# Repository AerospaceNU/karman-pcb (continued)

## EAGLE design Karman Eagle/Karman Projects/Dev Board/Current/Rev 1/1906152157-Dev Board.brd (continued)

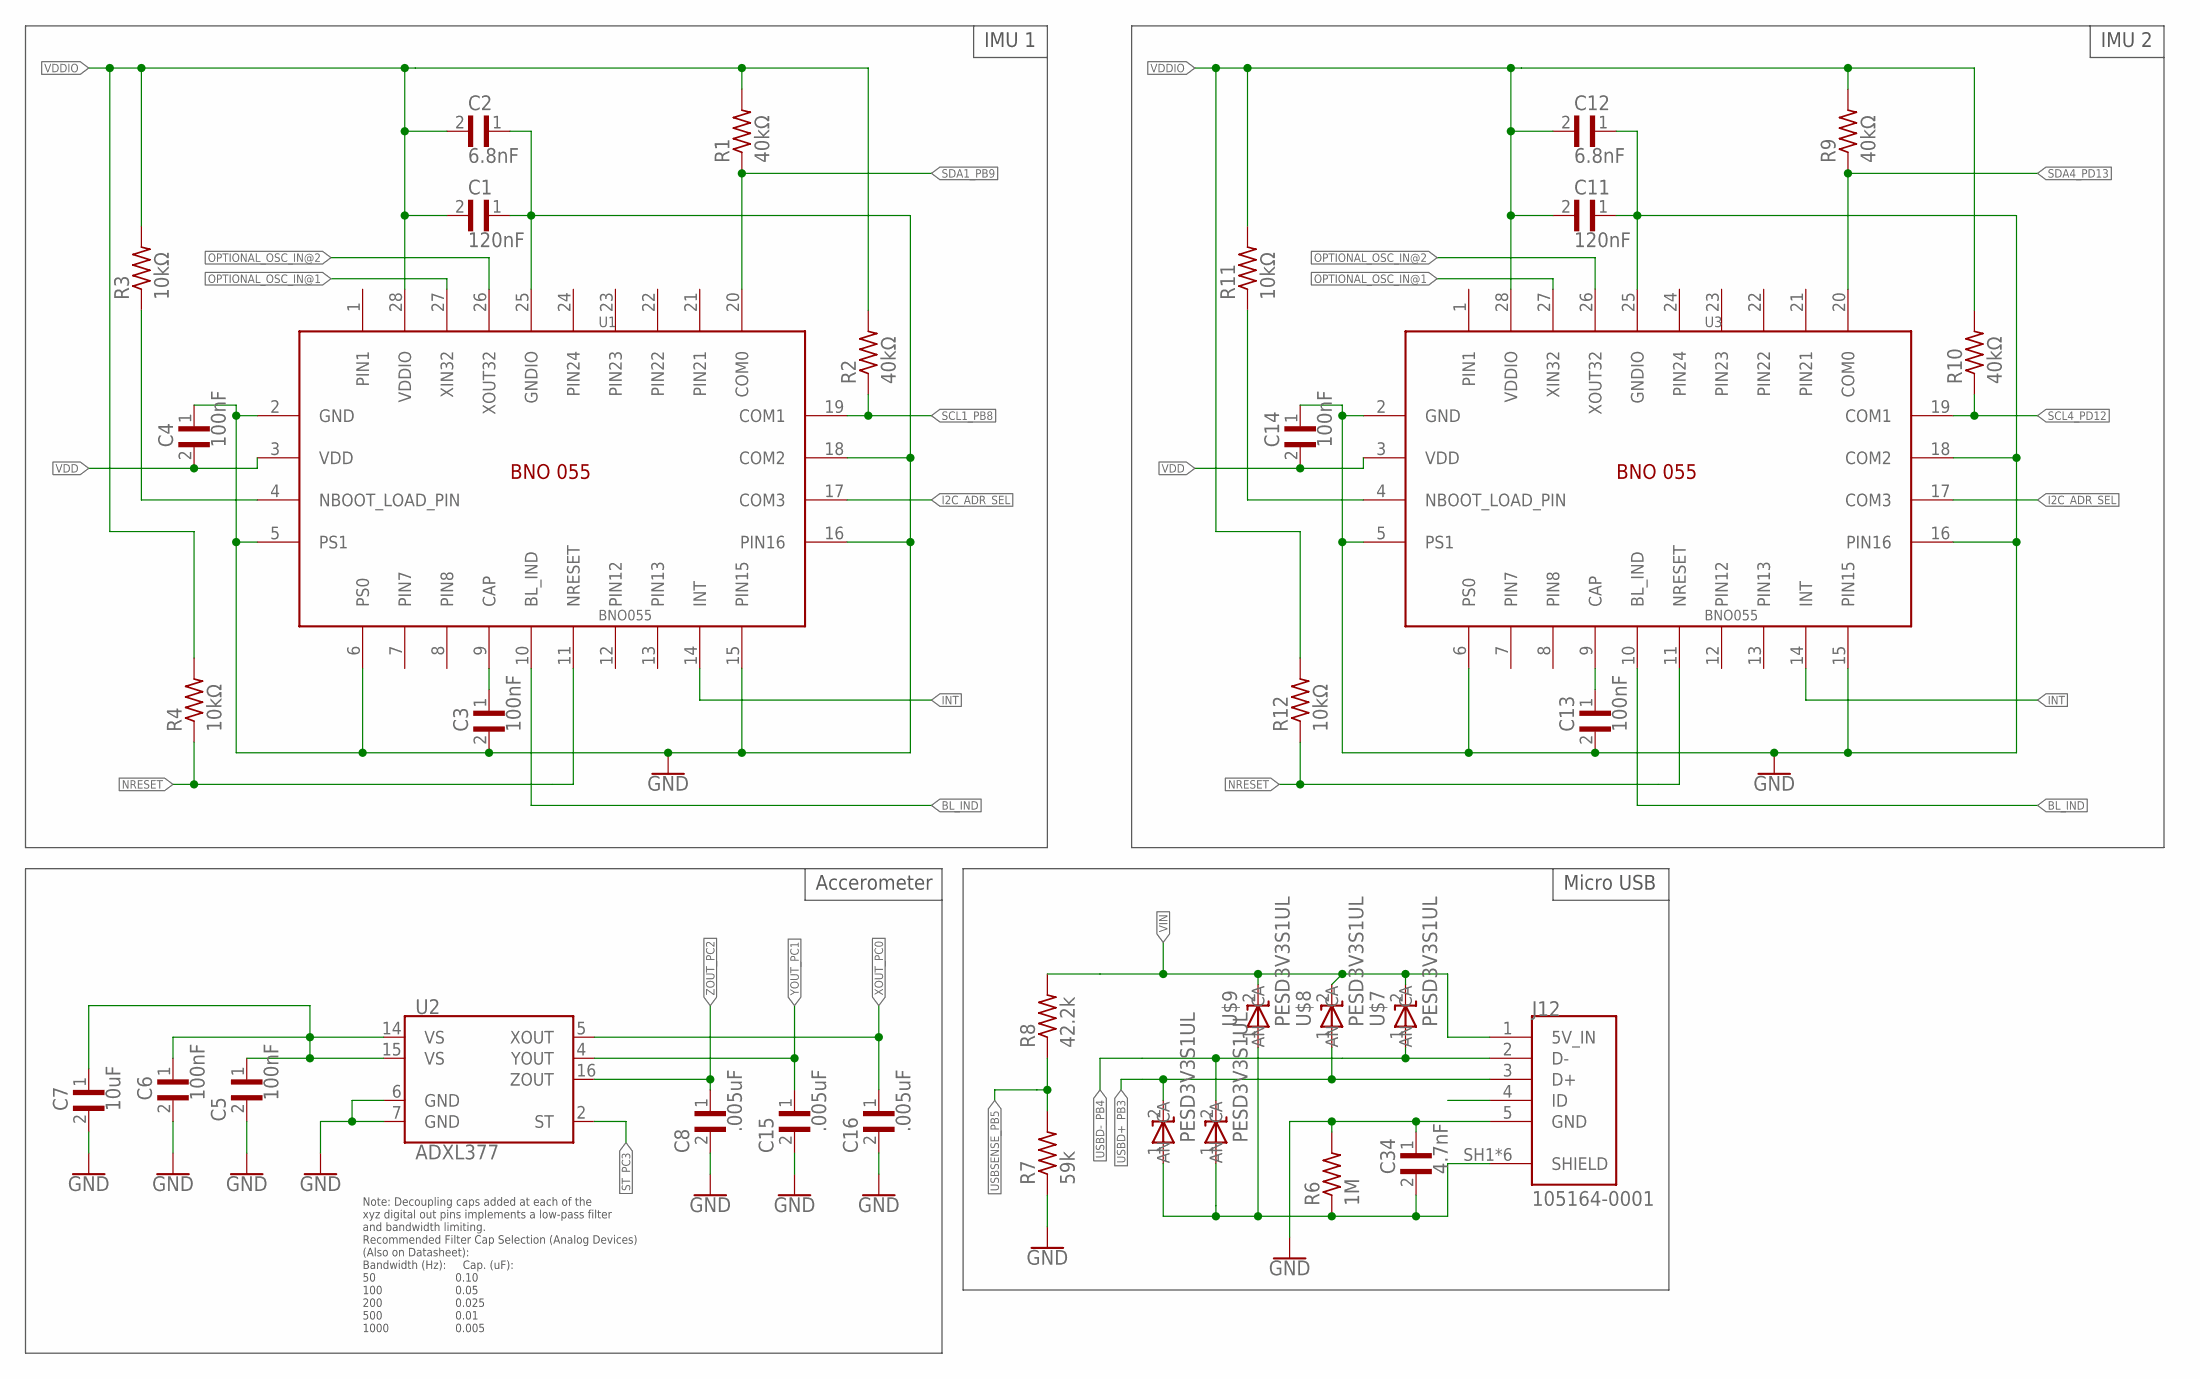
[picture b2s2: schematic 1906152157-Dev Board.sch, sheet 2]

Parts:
C1, C11: 120nF; CAPC1608X95N
C2, C12: 6.8nF; CAPC1608X95N
C3, C4, C5, C6, C13, C14: 100nF; CAPC1608X95N
C7: 10uF; CAPC1608X95N
C8, C15, C16: .005uF; CAPC1608X95N
C34: 4.7nF; CAPC1608X95N
J12: 105164-0001; MOLEX_105164-0001
R1, R2, R9, R10: 40kΩ; RESC1608X50N
R3, R4, R11, R12: 10kΩ; RESC1608X50N
R6: 1M; RESC1608X50N
R7: 59k; RESC1608X50N
R8: 42.2k; RESC1608X50N
U1, U3: BNO055; LGA28R50P4X10_380X520X100
U2: ADXL377; LFCSP-16-3X3
U$7, U$8, U$9, U$10, U$11: PESD3V3S1UL; SOD882

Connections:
BL_IND: U1.10 (BL_IND), U3.10 (BL_IND)
GND: C1.1, C2.1, C3.2, C4.1, C5.2, C6.2, C7.2, C8.2, C11.1, C12.1, C13.2, C14.1, C15.2, C16.2, C34.1, J12.5 (GND), R6.2, R7.1, U1.2 (GND), U1.5 (PS1), U1.6 (PS0), U1.15 (PIN15), U1.16 (PIN16), U1.18 (COM2), U1.25 (GNDIO), U2.6 (GND), U2.7 (GND), U3.2 (GND), U3.5 (PS1), U3.6 (PS0), U3.15 (PIN15), U3.16 (PIN16), U3.18 (COM2), U3.25 (GNDIO); also elsewhere on the board
I2C_ADR_SEL: U1.17 (COM3), U3.17 (COM3)
INT: U1.14 (INT), U3.14 (INT)
unnamed: C3.1, U1.9 (CAP)
unnamed: R3.1, U1.4 (NBOOT_LOAD_PIN)
unnamed: C13.1, U3.9 (CAP)
unnamed: R11.1, U3.4 (NBOOT_LOAD_PIN)
unnamed: C5.1, C6.1, C7.1, U2.14 (VS), U2.15 (VS)
unnamed: C34.2, J12.SH1 (SHIELD), J12.SH2 (SHIELD), J12.SH3 (SHIELD), J12.SH4 (SHIELD), J12.SH5 (SHIELD), J12.SH6 (SHIELD), R6.1, U$9.1 (CA), U$10.1 (CA), U$11.1 (CA)
NRESET: R4.1, R12.1, U1.11 (NRESET), U3.11 (NRESET)
OPTIONAL_OSC_IN@1: U1.27 (XIN32), U3.27 (XIN32)
OPTIONAL_OSC_IN@2: U1.26 (XOUT32), U3.26 (XOUT32)
PIN7: U1.7 (PIN7), U3.7 (PIN7)
PIN8: U1.8 (PIN8), U3.8 (PIN8)
PIN21: U1.21 (PIN21), U3.21 (PIN21)
PIN22: U1.22 (PIN22), U3.22 (PIN22)
PIN23: U1.23 (PIN23), U3.23 (PIN23)
PIN24: U1.24 (PIN24), U3.24 (PIN24)
SCL1_PB8: R2.1, U1.19 (COM1); also elsewhere on the board
SCL4_PD12: R10.1, U3.19 (COM1); also elsewhere on the board
SDA1_PB9: R1.1, U1.20 (COM0); also elsewhere on the board
SDA4_PD13: R9.1, U3.20 (COM0); also elsewhere on the board
ST_PC3: U2.2 (ST); also elsewhere on the board
USBD+_PB3: J12.3 (D+), U$8.1 (CA), U$11.2 (AN); also elsewhere on the board
USBD-_PB4: J12.2 (D-), U$7.1 (CA), U$10.2 (AN); also elsewhere on the board
USBSENSE_PB5: R7.2, R8.1; also elsewhere on the board
VDD: C4.2, C14.2, U1.3 (VDD), U3.3 (VDD)
VDDIO: C1.2, C2.2, C11.2, C12.2, R1.2, R2.2, R3.2, R4.2, R9.2, R10.2, R11.2, R12.2, U1.28 (VDDIO), U3.28 (VDDIO)
VIN: J12.1 (5V_IN), R8.2, U$7.2 (AN), U$8.2 (AN), U$9.2 (AN); also elsewhere on the board
XOUT_PC0: C16.1, U2.5 (XOUT); also elsewhere on the board
YOUT_PC1: C15.1, U2.4 (YOUT); also elsewhere on the board
ZOUT_PC2: C8.1, U2.16 (ZOUT); also elsewhere on the board

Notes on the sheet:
IMU 1
IMU 2
Note: Decoupling caps added at each of the xyz digital out pins implements a low-pass filter and bandwidth limiting. Recommended Filter Cap Selection (Analog Devices) (Also on Datasheet): Bandwidth (Hz): Cap. (uF): 50 0.10 100 0.05 200 0.025 500 0.01 1000 0.005
Accerometer
Micro USB

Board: 2 copper layers, 73 parts (1 on the bottom side), 78 nets, no tracks yet.

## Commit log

2019-05-06 David Antaki initial commit
2019-05-08 5/7/19-Updated FRIDAY Board
2019-05-14 5/13/19 Dev board update
2019-05-14 5/13/19 10:08PM Dev board update
2019-05-15 5/15/19 Add GPS-Radio Module
2019-05-25 5/24/19 20:26 PCB Update
2019-05-25 5/25/19 11:45 PCB Issued for Review
2019-05-25 5/25/19 12:47 PCB ISSUED FOR REVIEW
2019-06-16 BOM added
2019-08-03 DevBoard update 8/2/2019 11:59PM
2019-08-07 Rename README.md to README.txt
2020-05-07 Just some Eagle files that I never committed
